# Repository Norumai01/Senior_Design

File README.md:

# IDEAS for Good - ADAN Transport Cart Control System

## Copyright and Usage Notice
**© 2024 IDEAS for Good - ADAN Transport Project. All Rights Reserved.**

**CONFIDENTIAL AND PROPRIETARY**

This code and documentation contains confidential and proprietary information belonging to the IDEAS for Good - ADAN Transport Project. No part of this code may be copied, modified, distributed, or used in any manner without explicit written permission from the project maintainers. This code is provided for viewing purposes only and is protected under copyright law.

Unauthorized use, reproduction, or distribution of this code or any portion of it may result in severe civil and criminal penalties, and will be prosecuted to the maximum extent possible under the law.

## Overview
This project implements a control system for an electric transport cart using a Wii Nunchuck controller interface, managing motor control, gear selection, and various safety features through a CircuitPython-based implementation.

## Hardware Components
- **Microcontroller**: Adafruit Grand Central M4 Express
- **Controller**: Wii Nunchuck
- **Sensors**: BNO085 9-DOF Orientation IMU Fusion Sensor
- **Display**: 7-Segment LED Display
- **Motors**: Dual Motor System with PWM Control
- **Additional Components**: Buzzer, LED indicators, gear selection controls

## Pin Configuration
```python
# I2C Communication
i2c = board.I2C()  # uses board.SCL and board.SDA

# System Indicators
buzzer = board.D7
ledA = board.D6
ledB = board.D5
ledC = board.D4
ledD = board.D13
ledE = board.D10
ledF = board.D9
ledG = board.D8

# Motor Control
forPwm_1 = board.D24    # Forward PWM Motor 1
forPwm_2 = board.D25    # Forward PWM Motor 2
brakPwm_1 = board.D26   # Brake PWM Motor 1
brakPwm_2 = board.D27   # Brake PWM Motor 2

# Direction Control
Rev_1 = board.D28       # Reverse Motor 1
Rev_2 = board.D29       # Reverse Motor 2
softStart_1 = board.D30 # Soft Start Motor 1
softStart_2 = board.D31 # Soft Start Motor 2

# Gear Selection
gearSelect1_1 = board.D14
gearSelect1_2 = board.D15
gearSelect2_1 = board.D16
gearSelect2_2 = board.D17
```

## Features

### Motor Control System
- PWM-based speed control
- Soft start functionality
- Forward/Reverse operation
- Independent left/right motor control
- Progressive acceleration/deceleration
- Emergency braking system

### Gear System
- 10 gear modes (0-9):
  - Gears 1-3: Low speed range
  - Gears 4-6: Medium speed range
  - Gears 7-8: High speed range
  - Gears 0,9: Zero-point turning modes
- LED display indicates current gear
- Safety lockouts prevent gear changes while moving

### Control Interface
- Joystick-based directional control
- Button C: Forward/Reverse toggle
- Button Z: Gear selection
- Position-based speed control
- Steering through differential motor speed

### Safety Features
- Speed-dependent gear restrictions
- Movement lockout during gear changes
- Reverse warning buzzer
- Soft start protection
- Emergency brake system
- Zero-speed requirement for direction changes

## Operating Parameters
- PWM Frequency: 72 Hz
- PWM Range: 5500-9415 (duty cycle)
- Speed Ranges:
  - Low: 5800-6200
  - Medium: 5800-7000
  - High: 5800-8200
  - Zero-Point Turn: 6100-7200

## Control Logic
1. **Joystick Y-axis**:
   - Above 132: Forward motion
   - Below 124: Braking
   - 124-132: Neutral zone

2. **Joystick X-axis**:
   - Below 120: Left turn
   - Above 136: Right turn
   - 120-136: Straight motion

3. **Speed Control**:
   - Progressive acceleration based on joystick position
   - Automatic deceleration when returning to neutral
   - Emergency brake activation below y-axis 124

4. **Direction Changes**:
   - Only allowed at complete stop
   - Automatic buzzer activation in reverse
   - Debounced button inputs

## Software Implementation
The system is implemented in CircuitPython, providing:
- Non-blocking operation
- Real-time control response
- Smooth acceleration/deceleration
- Button debouncing
- PWM management
- Safety interlocks

## Future Improvements
- Integration with BNO085 orientation sensor for tilt protection
- Enhanced stability control
- Additional safety features
- Speed limiting based on orientation
- Improved user interface feedback

## Dependencies
- CircuitPython
- adafruit_nunchuk
- adafruit_simplemath
- pwmio
- busio
- digitalio

## Notes
- The system requires proper calibration of the Nunchuck controller
- PWM values are tuned for specific motor characteristics
- Safety features should be tested before deployment
- Regular maintenance checks recommended for optimal performance

---
**CONFIDENTIAL AND PROPRIETARY**  
All rights reserved. This code and documentation are protected by copyright law and international treaties. Any unauthorized use, reproduction, or distribution is strictly prohibited and may result in legal action.

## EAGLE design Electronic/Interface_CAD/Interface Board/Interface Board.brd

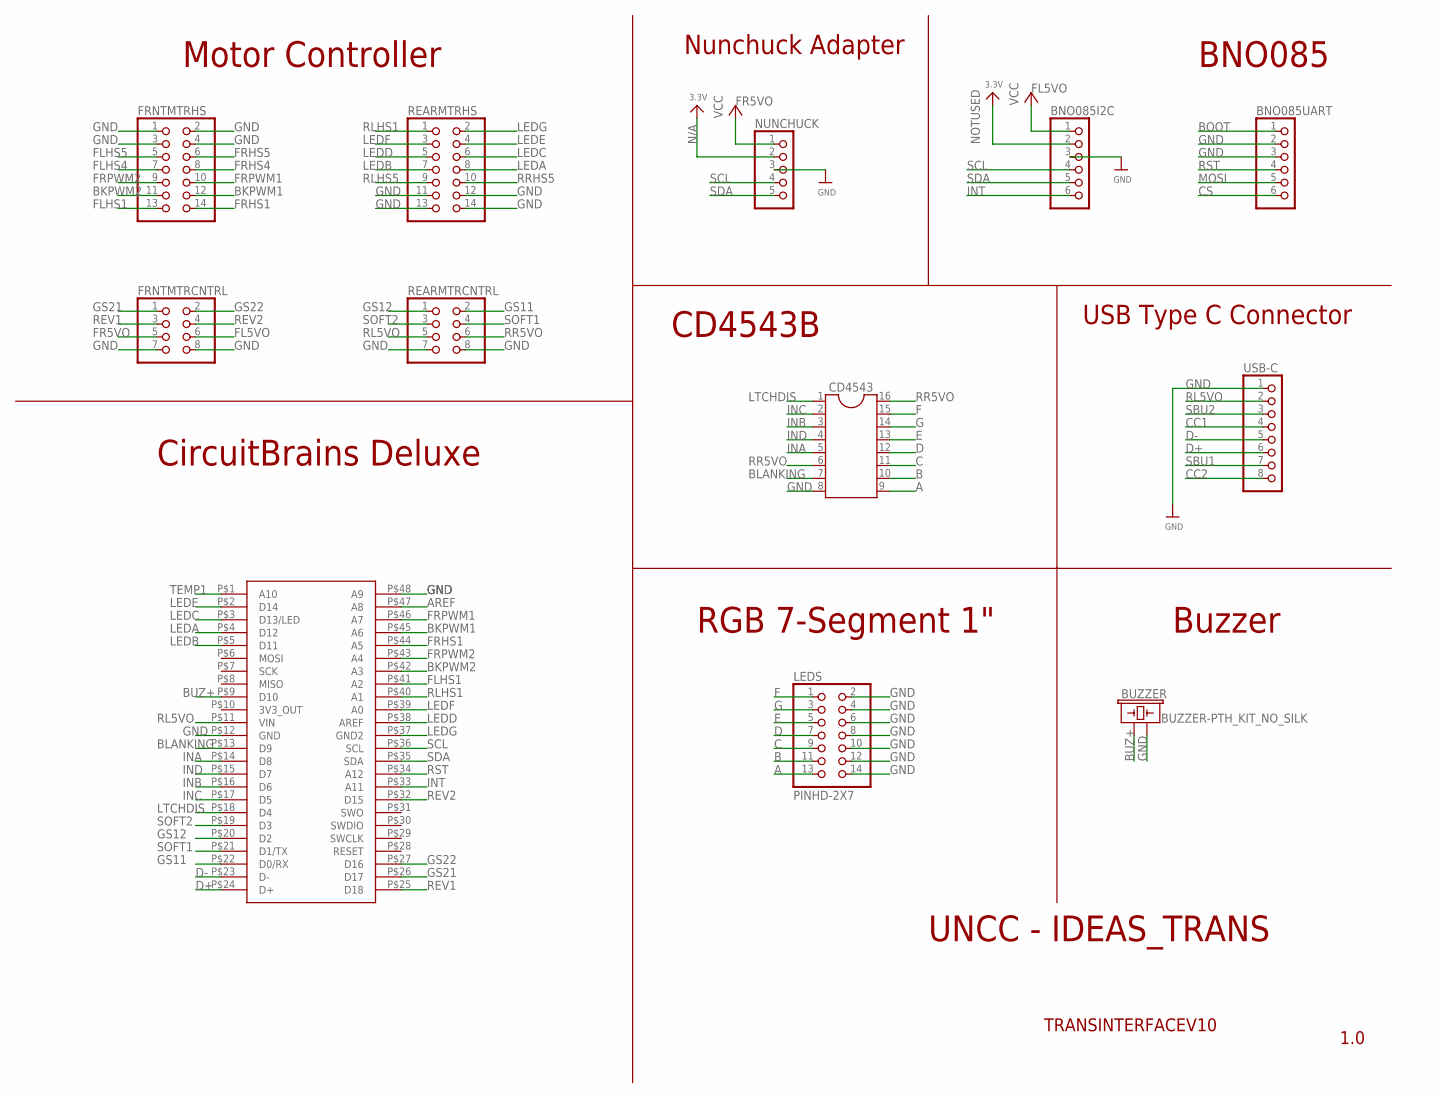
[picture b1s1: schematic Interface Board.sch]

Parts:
BNO085I2C, BNO085UART: HEADER-1X670MIL; 1X06_ROUND_70
BUZZER: BUZZER-PTH_KIT_NO_SILK; BUZZER-12MM-NS-KIT
CD4543: DIL16
FRNTMTRCNTRL: PINHD-2X4; 2X04
FRNTMTRHS: PINHD-2X7; 2X07
LEDS: PINHD-2X7; 2X07
NUNCHUCK: HEADER-1X570MIL; 1X05_ROUND_70
REARMTRCNTRL: PINHD-2X4; 2X04
REARMTRHS: PINHD-2X7; 2X07
U$1: CIRCUITBRAINS_DELUXEHANDSOLDER; DELUXE_48SOM_29MMX29MM_HANDSOLDER
USB-C: HEADER-1X876MIL; 1X08_ROUND_76

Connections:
3V3_OUT: U$1.P$10 (3V3_OUT)
A: CD4543.9, LEDS.13
AREF: U$1.P$47 (A8)
B: CD4543.10, LEDS.11
BKPWM1: FRNTMTRHS.12, U$1.P$45 (A6)
BKPWM2: FRNTMTRHS.11, U$1.P$42 (A3)
BLANKING: CD4543.7, U$1.P$13 (D9)
BOOT: BNO085UART.1
BUZ+: BUZZER.+ (1), U$1.P$9 (D10)
C: CD4543.11, LEDS.9
CC1: USB-C.4
CC2: USB-C.8
CS: BNO085UART.6
D: CD4543.12, LEDS.7
D+: U$1.P$24 (D+), USB-C.6
D-: U$1.P$23 (D-), USB-C.5
E: CD4543.13, LEDS.5
F: CD4543.15, LEDS.1
FL5VO: BNO085I2C.1, FRNTMTRCNTRL.6
FLHS1: FRNTMTRHS.13, U$1.P$41 (A2)
FLHS4: FRNTMTRHS.7
FLHS5: FRNTMTRHS.5
FR5VO: FRNTMTRCNTRL.5, NUNCHUCK.1
FRHS1: FRNTMTRHS.14, U$1.P$44 (A5)
FRHS4: FRNTMTRHS.8
FRHS5: FRNTMTRHS.6
FRPWM1: FRNTMTRHS.10, U$1.P$46 (A7)
FRPWM2: FRNTMTRHS.9, U$1.P$43 (A4)
G: CD4543.14, LEDS.3
GND: BNO085I2C.3, BNO085UART.2, BNO085UART.3, BUZZER.- (2), CD4543.8, FRNTMTRCNTRL.7, FRNTMTRCNTRL.8, FRNTMTRHS.1, FRNTMTRHS.2, FRNTMTRHS.3, FRNTMTRHS.4, LEDS.2, LEDS.4, LEDS.6, LEDS.8, LEDS.10, LEDS.12, LEDS.14, NUNCHUCK.3, REARMTRCNTRL.7, REARMTRCNTRL.8, REARMTRHS.11, REARMTRHS.12, REARMTRHS.13, REARMTRHS.14, U$1.P$12 (GND), U$1.P$48 (A9), USB-C.1
GS11: REARMTRCNTRL.2, U$1.P$22 (D0/RX)
GS12: REARMTRCNTRL.1, U$1.P$20 (D2)
GS21: FRNTMTRCNTRL.1, U$1.P$26 (D17)
GS22: FRNTMTRCNTRL.2, U$1.P$27 (D16)
INA: CD4543.5, U$1.P$14 (D8)
INB: CD4543.3, U$1.P$16 (D6)
INC: CD4543.2, U$1.P$17 (D5)
IND: CD4543.4, U$1.P$15 (D7)
INT: BNO085I2C.6, U$1.P$33 (A11)
LEDA: REARMTRHS.8, U$1.P$4 (D12)
LEDB: REARMTRHS.7, U$1.P$5 (D11)
LEDC: REARMTRHS.6, U$1.P$3 (D13/LED)
LEDD: REARMTRHS.5, U$1.P$38 (AREF)
LEDE: REARMTRHS.4, U$1.P$2 (D14)
LEDF: REARMTRHS.3, U$1.P$39 (A0)
LEDG: REARMTRHS.2, U$1.P$37 (GND2)
LTCHDIS: CD4543.1, U$1.P$18 (D4)
MOSI: BNO085UART.5
N/A: NUNCHUCK.2
NOTUSED: BNO085I2C.2
REV1: FRNTMTRCNTRL.3, U$1.P$25 (D18)
REV2: FRNTMTRCNTRL.4, U$1.P$32 (D15)
RL5VO: REARMTRCNTRL.5, U$1.P$11 (VIN), USB-C.2
RLHS1: REARMTRHS.1, U$1.P$40 (A1)
RLHS5: REARMTRHS.9
RR5VO: CD4543.6, CD4543.16, REARMTRCNTRL.6
RRHS5: REARMTRHS.10
RST: BNO085UART.4, U$1.P$34 (A12)
SBU1: USB-C.7
SBU2: USB-C.3
SCL: BNO085I2C.4, NUNCHUCK.4, U$1.P$36 (SCL)
SDA: BNO085I2C.5, NUNCHUCK.5, U$1.P$35 (SDA)
SOFT1: REARMTRCNTRL.4, U$1.P$21 (D1/TX)
SOFT2: REARMTRCNTRL.3, U$1.P$19 (D3)
TEMP1: U$1.P$1 (A10)

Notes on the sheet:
1.0
TRANSINTERFACEV10
UNCC - IDEAS_TRANS
BNO085
Nunchuck Adapter
Motor Controller
USB Type C Connector
CD4543B
RGB 7-Segment 1"
Buzzer
CircuitBrains Deluxe

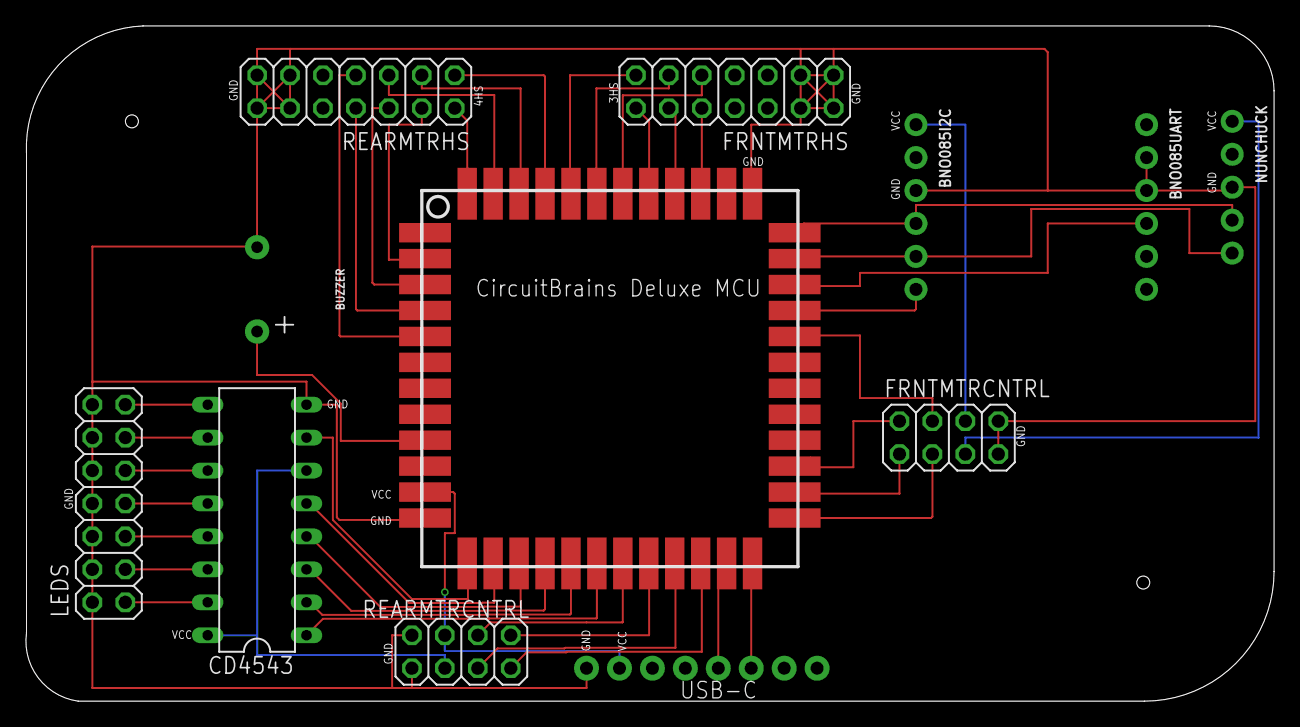
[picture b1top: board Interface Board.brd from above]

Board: 2 copper layers, 96.2 x 52.1 mm, 12 parts (0 on the bottom side), 47 nets.

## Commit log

2023-04-12 Uploaded testing code and started drive system.
2023-04-12 Deleted files, this branch will merge to main.
2023-11-03 Added main control file.
2023-12-04 Updated github with latest test files of the cart.
2023-12-04 Organized Folder
2023-12-04 Fixed typos within code.
2024-03-18 Final Edit to Senior Design Code.
2024-03-18 Documentation added to Senior Design.
2024-10-27 Updated README file

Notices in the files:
parts and their libraries:
microbuilder: This work is placed in the public domain, and may be freely used for commercial and non-commercial work with the following conditions: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
SparkFun-Electromechanical: Licensing: Creative Commons ShareAlike 4.0 International - https://creativecommons.org/licenses/by-sa/4.0
